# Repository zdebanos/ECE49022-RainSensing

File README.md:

# ECE49022 Rain Sensing Project

TODO.
Central GitHub repository for the ECE49022 Project.

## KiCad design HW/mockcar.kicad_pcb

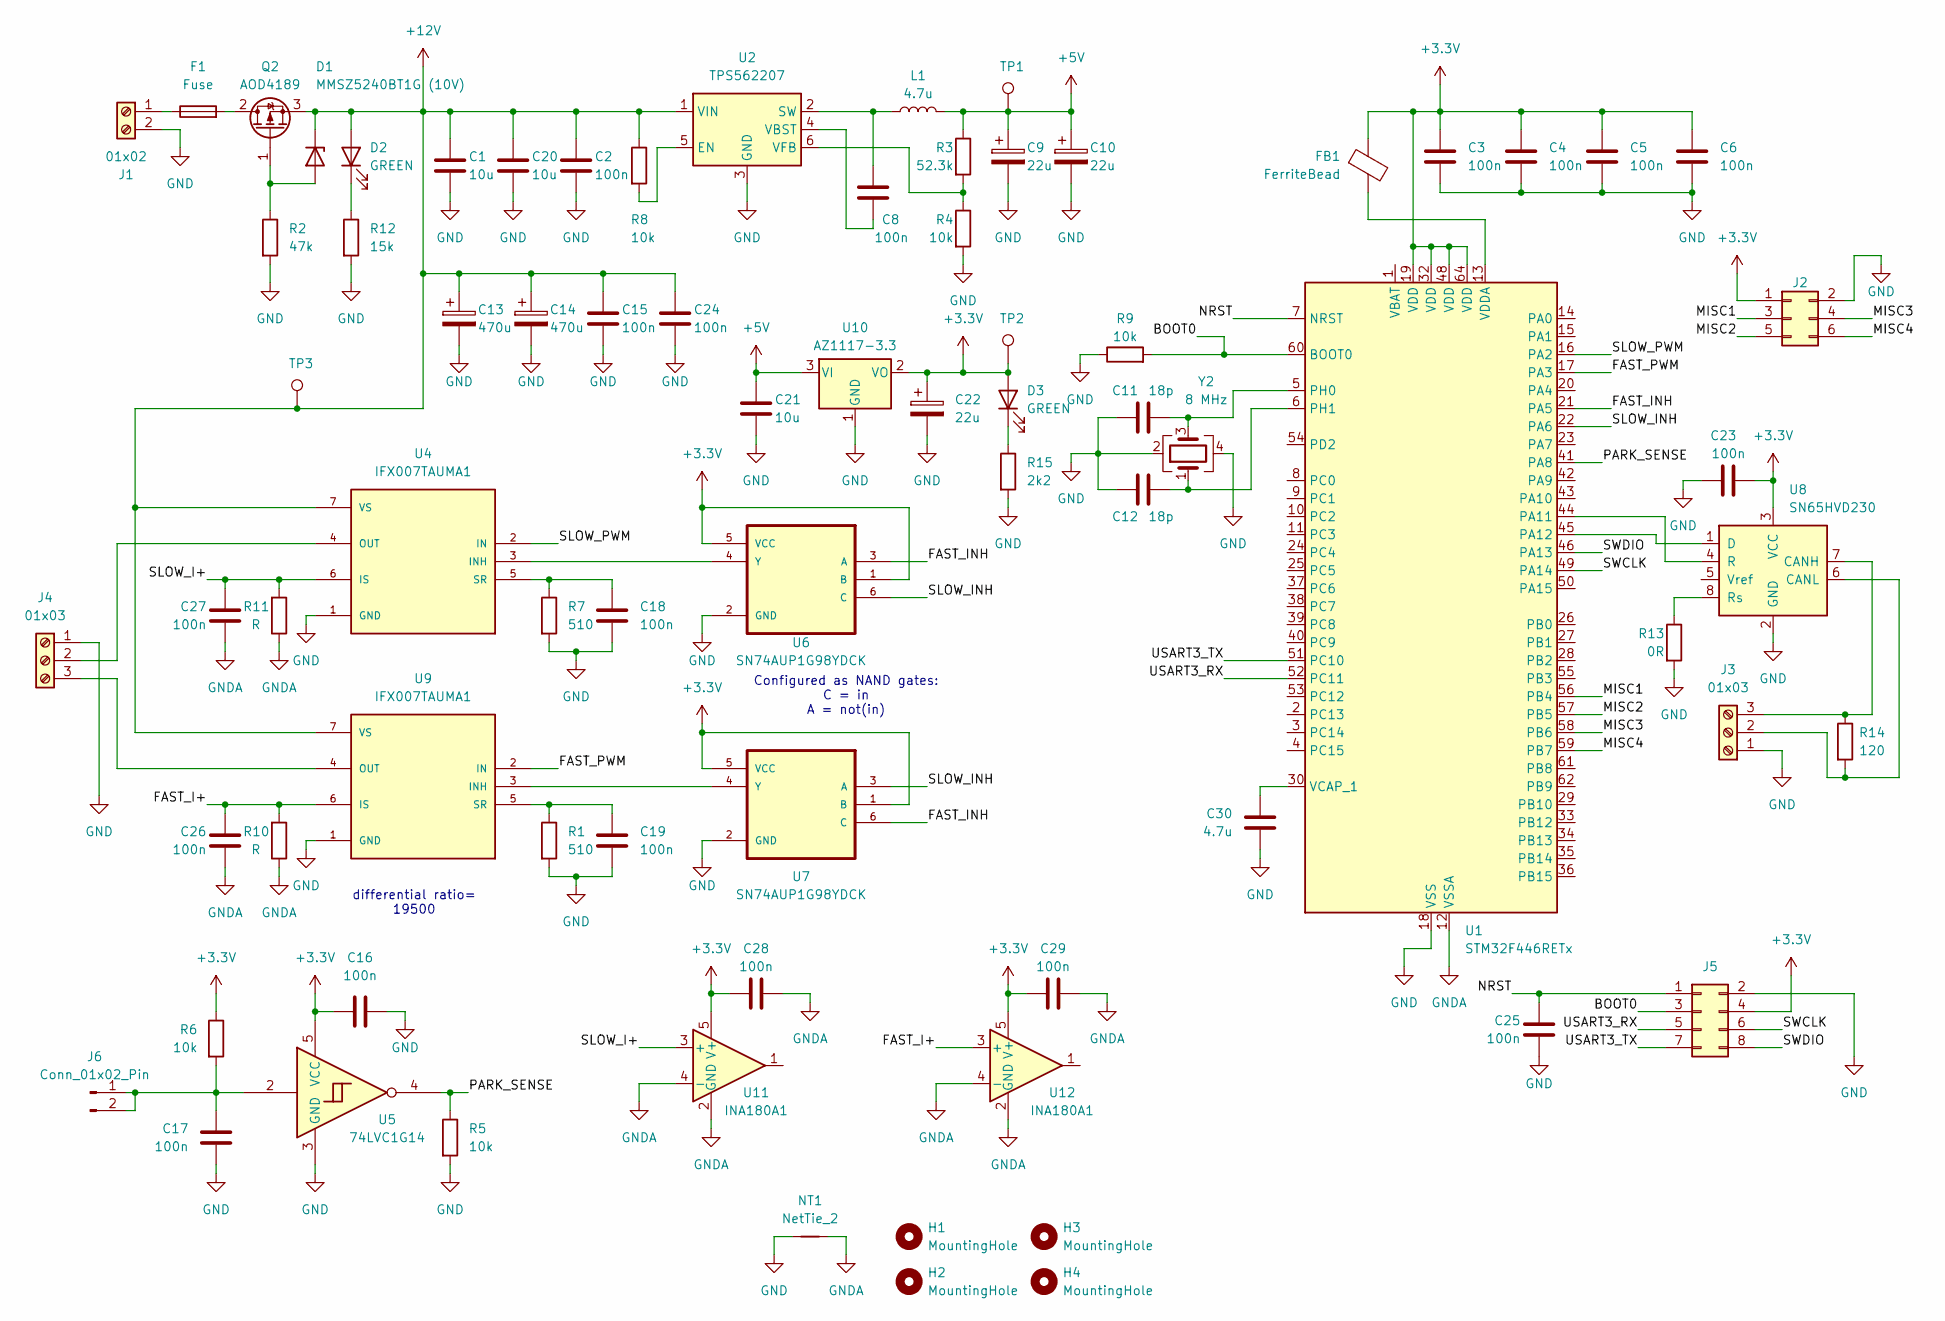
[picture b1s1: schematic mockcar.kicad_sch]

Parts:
C1, C20, C21: 10u; C_0805_2012Metric
C2, C3, C4, C5, C6, C8, C15, C16, C17, C18, C19, C23, C24, C25, C26, C27, C28, C29: 100n; C_0805_2012Metric
C9, C10, C22: 22u; C_1206_3216Metric
C11, C12: 18p; C_0603_1608Metric
C13, C14: 470u; C_Radial_D10.0mm_H16.0mm_P5.00mm
C30: 4.7u; C_0805_2012Metric
D1: MMSZ5240BT1G (10V); Nexperia_CFP3_SOD-123W
D2, D3: GREEN; LED_0603_1608Metric
F1: Fuse; Fuse_2512_6332Metric
FB1: FerriteBead; R_0805_2012Metric
H1, H2, H3, H4: MountingHole; MountingHole_2.2mm_M2_DIN965_Pad_TopBottom
J1: 01x02; TerminalBlock_MaiXu_MX126-5.0-02P_1x02_P5.00mm
J2: Conn_02x03_Odd_Even; PinHeader_2x03_P2.54mm_Vertical
J3: 01x03; Molex_KK-254_AE-6410-03A_1x03_P2.54mm_Vertical
J4: 01x03; TerminalBlock_MaiXu_MX126-5.0-03P_1x03_P5.00mm
J5: Conn_02x04_Odd_Even; PinHeader_2x04_P2.00mm_Vertical
J6: Conn_01x02_Pin; Molex_KK-254_AE-6410-02A_1x02_P2.54mm_Vertical
L1: 4.7u; L_1210_3225Metric
NT1: NetTie_2; NetTie-2_SMD_Pad2.0mm
Q2: AOD4189; TO-252-2
R1, R7: 510; R_0805_2012Metric
R2: 47k; R_0805_2012Metric
R3: 52.3k; R_0805_2012Metric
R4, R5, R6, R8, R9: 10k; R_0805_2012Metric
R10, R11: R; R_0805_2012Metric
R12: 15k; R_0805_2012Metric
R13: 0R; R_0805_2012Metric
R14: 120; R_0805_2012Metric
R15: 2k2; R_0805_2012Metric
TP1, TP2, TP3: TestPoint; TestPoint_Pad_D1.0mm
U1: STM32F446RETx; LQFP-64_10x10mm_P0.5mm
U2: TPS562207; SOT-563
U4, U9: IFX007TAUMA1; PARTREV 1.0
U5: 74LVC1G14; SOT-353_SC-70-5
U6, U7: SN74AUP1G98YDCK; SOT-363_SC-70-6
U8: SN65HVD230; SOIC-8_3.9x4.9mm_P1.27mm
U10: AZ1117-3.3; SOT-223-3_TabPin2
U11, U12: INA180A1; SOT-23-5
Y2: 8 MHz; Crystal_SMD_3225-4Pin_3.2x2.5mm

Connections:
+3.3V: C3.1, C4.1, C5.1, C6.1, C16.1, C22.1, C23.2, C28.1, C29.1, D3.2 (A), FB1.1, J2.1, J5.4, R6.1, TP2.1, U1.19 (VDD), U1.32 (VDD), U1.48 (VDD), U1.64 (VDD), U5.5 (VCC), U6.1 (B), U6.5 (VCC), U7.1 (B), U7.5 (VCC), U8.3 (VCC), U10.2 (VO), U11.5 (V+), U12.5 (V+)
+5V: C9.1, C10.1, C21.1, L1.2, R3.1, TP1.1, U10.3 (VI)
+12V: C1.1, C2.1, C13.1, C14.1, C15.1, C20.1, C24.1, D1.1 (K), D2.2 (A), Q2.3 (S), R8.1, TP3.1, U2.1 (VIN), U4.7 (VS), U9.7 (VS)
/BOOT0: J5.3, R9.2, U1.60 (BOOT0)
/FAST_I+: C26.2, R10.2, U9.6 (IS), U12.3 (+)
/FAST_INH: U1.21 (PA5), U6.3 (A), U7.6 (C)
/FAST_PWM: U1.17 (PA3), U9.2 (IN)
/MISC1: J2.3, U1.56 (PB4)
/MISC2: J2.5, U1.57 (PB5)
/MISC3: J2.4, U1.58 (PB6)
/MISC4: J2.6, U1.59 (PB7)
/NRST: C25.1, J5.1, U1.7 (NRST)
/PARK_SENSE: R5.1, U1.41 (PA8), U5.4
/SLOW_I+: C27.2, R11.2, U4.6 (IS), U11.3 (+)
/SLOW_INH: U1.22 (PA6), U6.6 (C), U7.3 (A)
/SLOW_PWM: U1.16 (PA2), U4.2 (IN)
/SWCLK: J5.6, U1.49 (PA14)
/SWDIO: J5.8, U1.46 (PA13)
/USART3_RX: J5.5, U1.52 (PC11)
/USART3_TX: J5.7, U1.51 (PC10)
GND: C1.2, C2.2, C3.2, C4.2, C5.2, C6.2, C9.2, C10.2, C11.1, C12.1, C13.2, C14.2, C15.2, C16.2, C17.1, C18.2, C19.2, C20.2, C21.2, C22.2, C23.1, C24.2, C25.2, C30.2, J1.2, J2.2, J3.1, J4.1, J5.2, NT1.1, R1.2, R2.2, R4.2, R5.2, R7.2, R9.1, R12.2, R13.2, R15.2, U1.18 (VSS), U1.31 (VSS), U1.47 (VSS), U1.63 (VSS), U2.3 (GND), U4.1 (GND), U5.3 (GND), U6.2 (GND), U7.2 (GND), U8.2 (GND), U9.1 (GND), U10.1 (GND), Y2.2, Y2.4
GNDA: C26.1, C27.1, C28.2, C29.2, NT1.2, R10.1, R11.1, U1.12 (VSSA), U11.2 (GND), U11.4 (-), U12.2 (GND), U12.4 (-)
unnamed: D1.2 (A), Q2.1 (G), R2.1
unnamed: D2.1 (K), R12.1
unnamed: D3.1 (K), R15.1
unnamed: F1.1, J1.1
unnamed: J3.2, R14.2, U8.6 (CANL)
unnamed: J3.3, R14.1, U8.7 (CANH)
unnamed: J4.2, U4.4 (OUT), U4.8 (OUT)
unnamed: J4.3, U9.4 (OUT), U9.8 (OUT)
unnamed: C17.2, J6.1, J6.2, R6.2, U5.2
unnamed: F1.2, Q2.2 (D)
unnamed: U1.44 (PA11), U8.4 (R)
unnamed: U1.45 (PA12), U8.1 (D)
unnamed: C11.2, U1.5 (PH0), Y2.3
unnamed: C12.2, U1.6 (PH1), Y2.1
unnamed: C30.1, U1.30 (VCAP_1)
unnamed: FB1.2, U1.13 (VDDA)
unnamed: R8.2, U2.5 (EN)
unnamed: C8.2, L1.1, U2.2 (SW)
unnamed: C8.1, U2.4 (VBST)
unnamed: R3.2, R4.1, U2.6 (VFB)
unnamed: U4.3 (INH), U6.4 (Y)
unnamed: C18.1, R7.1, U4.5 (SR)
unnamed: U7.4 (Y), U9.3 (INH)
unnamed: R13.1, U8.8 (Rs)
unnamed: C19.1, R1.1, U9.5 (SR)

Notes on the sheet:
Configured as NAND gates: C = in A = not(in)
differential ratio= 19500

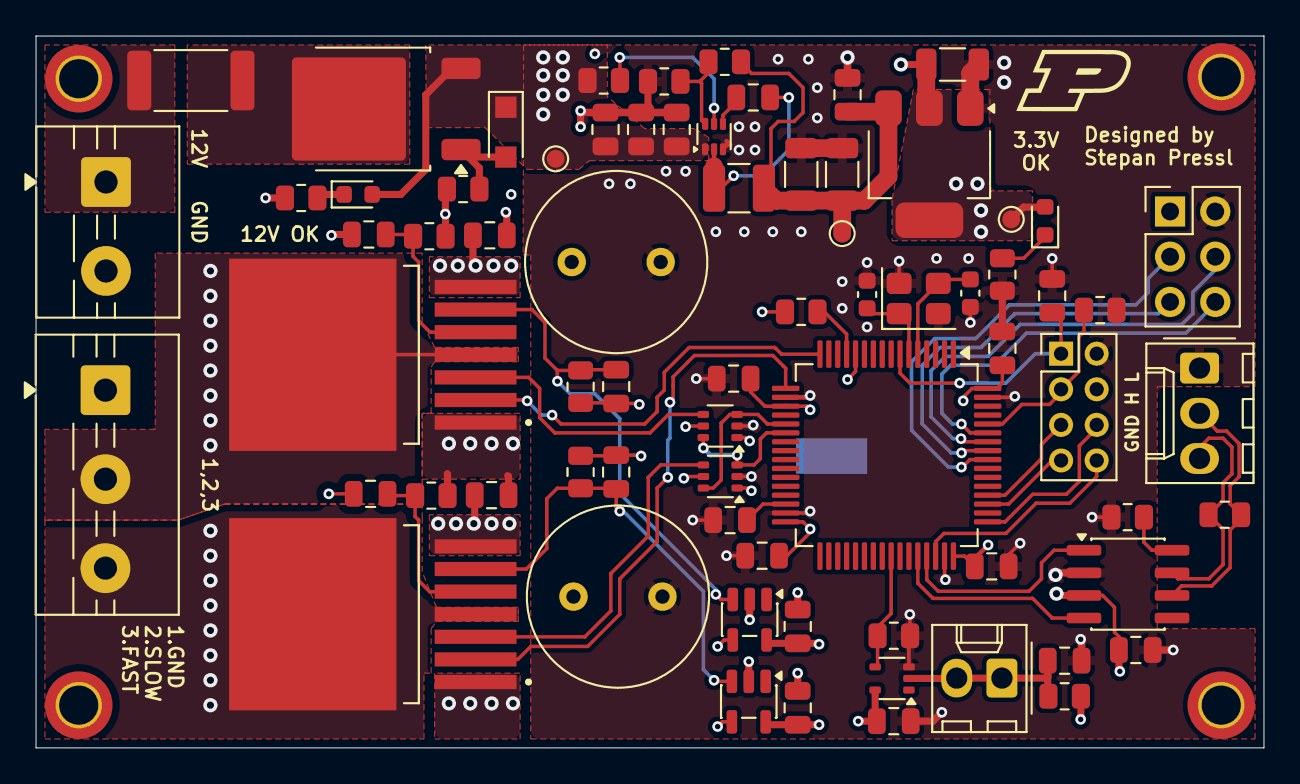
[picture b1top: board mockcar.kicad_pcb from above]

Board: 4 copper layers, 69.0 x 40.0 mm, 77 parts (1 on the bottom side), 47 nets.

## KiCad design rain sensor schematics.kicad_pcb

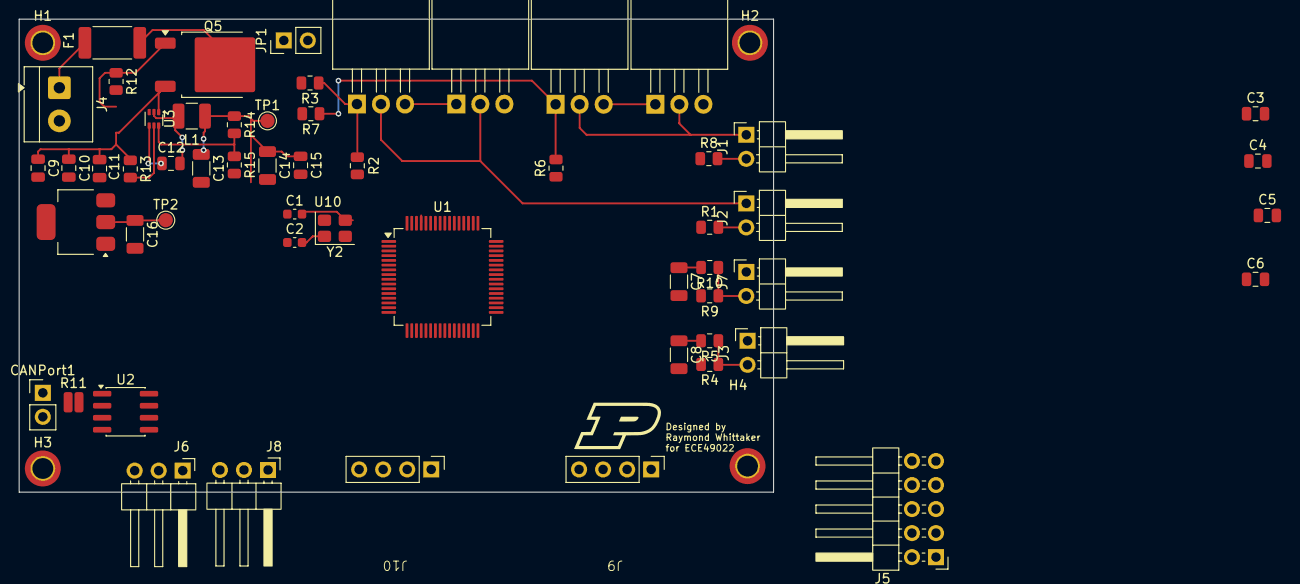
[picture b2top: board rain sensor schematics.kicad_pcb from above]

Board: 2 copper layers, 79.8 x 50.0 mm, 62 parts (1 on the bottom side), 35 nets.

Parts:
C1, C2: 18p; C_0603_1608Metric
C3, C4, C5, C6: C; C_0805_2012Metric
C7, C8: 1u; C_1206_3216Metric
C9, C10, C15: 10u; C_0805_2012Metric
C11, C12: 100n; C_0805_2012Metric
C13, C14, C16: 22u; C_1206_3216Metric
CANPort1: Conn_01x02_Pin; PinHeader_1x02_P2.54mm_Vertical
D1: MMSZ5240BT1G (10V); Nexperia_CFP3_SOD-123W
F1: Fuse; Fuse_2512_6332Metric
H1, H2, H3, H4: MountingHole; MountingHole_2.2mm_M2_ISO14580_Pad_TopBottom
J1, J2, J3, J7: Conn_01x02_Pin; PinHeader_1x02_P2.54mm_Horizontal
J4: 01x02; TerminalBlock_4Ucon_1x02_P3.50mm_Horizontal
J5: LCD Screen Jumpers; PinHeader_2x05_P2.54mm_Horizontal
J6: Vib. Sens 1; PinHeader_1x03_P2.54mm_Horizontal
J8: Vib. Sens 2; PinHeader_1x03_P2.54mm_Horizontal
J9: Rain Sens 1; Rain_Sensor_footprint
J10: Rain Sens 2; Rain_Sensor_footprint
JP1: NO; PinHeader_1x02_P2.54mm_Vertical
L1: 4.7u; L_1210_3225Metric
Q1, Q2, Q3, Q4: TIP120; TO-220-3_Horizontal_TabDown
Q5: AOD4189; TO-252-2
R1, R8: 15; R_0805_2012Metric
R2, R3, R6, R7: 1k; R_0805_2012Metric
R4, R9: 270k; R_0805_2012Metric
R5, R10: 100k; R_0805_2012Metric
R11: 120; R_0508_1220Metric
R12: 47k; R_0805_2012Metric
R13, R15: 10k; R_0805_2012Metric
R14: 52.3k; R_0805_2012Metric
TP1, TP2: TestPoint; TestPoint_Pad_D1.5mm
U1: STM32F446RETx; LQFP-64_10x10mm_P0.5mm
U2: SN65HVD230; SOIC-8_3.9x4.9mm_P1.27mm
U3: TPS562207; SOT-563
U10: AZ1117-3.3; SOT-223-3_TabPin2
Y2: 8 MHz; Crystal_SMD_3225-4Pin_3.2x2.5mm

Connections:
+3.3V: C3.1, C4.1, C5.1, C6.1, C16.1, J3.1, J6.2, J7.1, J8.2, J9.4, J10.4, TP2.1, U1.19 (VDD), U1.32 (VDD), U1.48 (VDD), U1.64 (VDD), U2.3 (VCC), U10.2 (VO)
+5V: C13.1, C14.1, C15.1, L1.2, R14.1, TP1.1, U10.3 (VI)
+12V: R1.1, R8.1
/LED Receiver Circuit/IR_Sense_1: C7.1, R10.2
/LED Receiver Circuit/IR_Sense_2: C8.1, R5.2
GND: C1.1, C2.1, C3.2, C4.2, C5.2, C6.2, C7.2, C8.2, C9.2, C10.2, C11.2, C13.2, C14.2, C15.2, C16.2, J4.2, J6.1, J8.1, J9.1, J10.1, JP1.1 (A), Q2.3 (E), Q4.3 (E), R3.2, R4.2, R7.2, R9.2, R12.2, R15.2, U1.18 (VSS), U1.31 (VSS), U1.47 (VSS), U1.63 (VSS), U2.2 (GND), U2.8 (Rs), U3.3 (GND), U10.1 (GND), Y2.2, Y2.4
unnamed: CANPort1.1, R11.2, U2.6 (CANL)
unnamed: CANPort1.2, R11.1, U2.7 (CANH)
unnamed: D1.2 (A), Q5.1 (G), R12.1
unnamed: C9.1, C10.1, C11.1, D1.1 (K), Q5.3 (S), R13.1, U3.1 (VIN)
unnamed: J1.1, Q3.2 (C), Q4.2 (C)
unnamed: J1.2, R8.2
unnamed: J2.1, Q1.2 (C), Q2.2 (C)
unnamed: J2.2, R1.2
unnamed: J3.2, R4.1, R5.1
unnamed: F1.1, J4.1
unnamed: J6.3, U1.14 (PA0)
unnamed: J7.2, R9.1, R10.1
unnamed: J8.3, U1.15 (PA1)
unnamed: J9.3, U1.42 (PA9)
unnamed: J10.3, U1.57 (PB5)
unnamed: JP1.2 (B), U1.60 (BOOT0)
unnamed: Q1.1 (B), R2.2, R3.1
unnamed: Q1.3 (E), Q2.1 (B)
unnamed: Q3.1 (B), R6.2, R7.1
unnamed: Q3.3 (E), Q4.1 (B)
unnamed: F1.2, Q5.2 (D)
unnamed: U1.61 (PB8), U2.4 (R)
unnamed: U1.62 (PB9), U2.1 (D)
unnamed: C1.2, U1.5 (PH0), Y2.3
unnamed: C2.2, U1.6 (PH1), Y2.1
unnamed: R13.2, U3.5 (EN)
unnamed: C12.2, L1.1, U3.2 (SW)
unnamed: C12.1, U3.4 (VBST)
unnamed: R14.2, R15.1, U3.6 (VFB)

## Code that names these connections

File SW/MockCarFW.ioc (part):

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Mcu.Name=STM32F446R(C-E)Tx
Mcu.Package=LQFP64
Mcu.UserName=STM32F446RETx
PA11.Mode=CAN_Activate
PA11.Signal=CAN1_RX
PA12.Mode=CAN_Activate
PA12.Signal=CAN1_TX
PA2.Signal=GPIO_Output
PA3.Signal=GPIO_Output
PA5.Signal=GPIO_Output
PA6.Signal=GPIO_Output
PA8.Signal=GPXTI8
PC10.Mode=Asynchronous
PC10.Signal=USART3_TX
PC11.Mode=Asynchronous
PC11.Signal=USART3_RX
board=custom

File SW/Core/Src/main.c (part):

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	switch (speed) {
	case WIPERS_SLOW:
	case WIPERS_MEDIUM:
		HAL_GPIO_WritePin(FAST_INH_PORT, FAST_INH_PIN, GPIO_PIN_RESET);
		HAL_GPIO_WritePin(SLOW_INH_PORT, SLOW_INH_PIN, GPIO_PIN_SET);
		HAL_GPIO_WritePin(SLOW_PWM_PORT, SLOW_PWM_PIN, GPIO_PIN_SET);
		HAL_GPIO_WritePin(FAST_PWM_PORT, FAST_PWM_PIN, GPIO_PIN_RESET);
		break;
	case WIPERS_FAST:
		HAL_GPIO_WritePin(FAST_INH_PORT, FAST_INH_PIN, GPIO_PIN_SET);
		HAL_GPIO_WritePin(SLOW_INH_PORT, SLOW_INH_PIN, GPIO_PIN_RESET);
		HAL_GPIO_WritePin(SLOW_PWM_PORT, SLOW_PWM_PIN, GPIO_PIN_RESET);
		HAL_GPIO_WritePin(FAST_PWM_PORT, FAST_PWM_PIN, GPIO_PIN_SET);
		break;
	default: /* Ignore OFF */
		break;
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			HAL_TIM_Base_Stop(&htim7);
			check_park_after = false;
			/* Check the polarity of the edge */
			if (HAL_GPIO_ReadPin(PARK_SENSE_PORT, PARK_SENSE_PIN) == GPIO_PIN_SET) {
				/* This means the motor is parked in the park position. However,
				 * stop the motor if it's requested, otherwise not.
				 */
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		} else {
			if (stop_motor) {
				/* Caught stop motor condition, disable everything */
				HAL_GPIO_WritePin(SLOW_PWM_PORT, SLOW_PWM_PIN, GPIO_PIN_RESET);
				HAL_GPIO_WritePin(FAST_PWM_PORT, FAST_PWM_PIN, GPIO_PIN_RESET);
				wipers_state = WIPERS_PARKED;
				if (wipers_speed == WIPERS_SLOW) {
					/* Start the countdown slow timer */
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  /*Configure GPIO pin Output Level */
  HAL_GPIO_WritePin(GPIOA, GPIO_PIN_2|GPIO_PIN_3|GPIO_PIN_5|GPIO_PIN_6, GPIO_PIN_RESET);

  /*Configure GPIO pins : PA2 PA3 PA5 PA6 */
  GPIO_InitStruct.Pin = GPIO_PIN_2|GPIO_PIN_3|GPIO_PIN_5|GPIO_PIN_6;
  GPIO_InitStruct.Mode = GPIO_MODE_OUTPUT_PP;
  GPIO_InitStruct.Pull = GPIO_NOPULL;
  GPIO_InitStruct.Speed = GPIO_SPEED_FREQ_LOW;
  HAL_GPIO_Init(GPIOA, &GPIO_InitStruct);

  /*Configure GPIO pin : PA8 */
  GPIO_InitStruct.Pin = GPIO_PIN_8;
  GPIO_InitStruct.Mode = GPIO_MODE_IT_RISING;
  GPIO_InitStruct.Pull = GPIO_NOPULL;
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
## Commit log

2026-01-22 Initial README commit
2026-02-19 Add user interface schematic
2026-03-03 Enhance button press handling and display updates
    Refactor main.c to include additional functionality for button press handling and update display messages accordingly.
2026-03-04 Remove unnecessary comments and clean up code
2026-03-04 Rename Screenshot 2026-03-04 183138.png to Katie_Kicad_Schematic
2026-03-05 MockCar: add STM32Cube HAL demo fw
2026-04-11 FW: update firmware to the final PCB HW
2026-04-11 HW: add the mockcar kicad project
2026-04-14 Add files via upload
    Mock car main
2026-04-24 Another FW iteration

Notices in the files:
SW/Core/Src/main.c:
Copyright (c) 2026 STMicroelectronics.
All rights reserved.
This software is licensed under terms that can be found in the LICENSE file
